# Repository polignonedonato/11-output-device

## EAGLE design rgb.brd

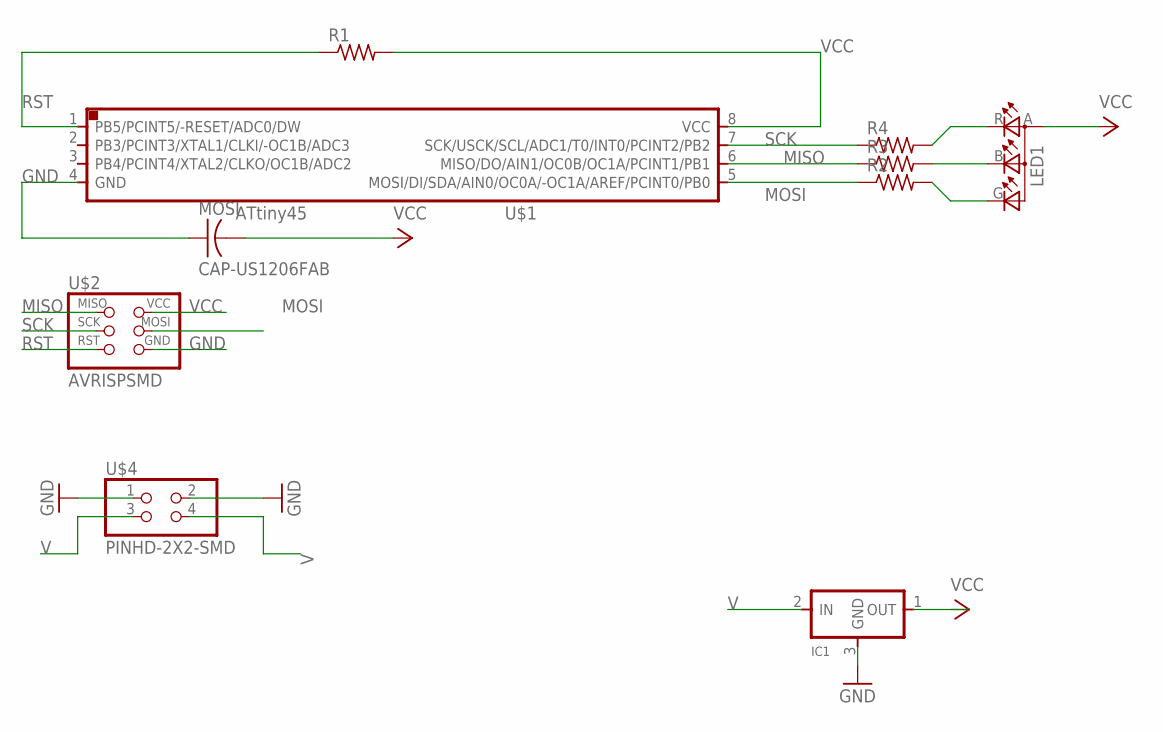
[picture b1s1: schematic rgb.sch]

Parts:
IC1: REGULATORSOT23; SOT23
LED1: LEDRGBOLD; P-LCC-4-3
MOSI: CAP-US1206FAB; C1206FAB
R1, R2, R3, R4: RES-US1206FAB; R1206FAB
U$1: ATTINY45SI; SOIC8
U$2: AVRISPSMD; 2X03SMD
U$4: PINHD-2X2-SMD; 2X02SMD

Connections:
GND: IC1.3 (GND), MOSI.1, U$1.4 (GND), U$2.6 (GND), U$4.1, U$4.2
MISO: R3.1, U$1.6 (MISO/DO/AIN1/OC0B/OC1A/PCINT1/PB1), U$2.1 (MISO)
MOSI: R2.1, U$1.5 (MOSI/DI/SDA/AIN0/OC0A/-OC1A/AREF/PCINT0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), U$2.4 (MOSI)
unnamed: LED1.R (CRED), R4.2
unnamed: LED1.G (CGREEN), R2.2
unnamed: LED1.B (CBLUE), R3.2
RST: R1.1, U$1.1 (PB5/PCINT5/-RESET/ADC0/DW), U$2.5 (RST)
SCK: R4.1, U$1.7 (SCK/USCK/SCL/ADC1/T0/INT0/PCINT2/PB2), U$2.3 (SCK)
V: IC1.2 (IN), U$4.3, U$4.4
VCC: LED1.A (A2), MOSI.2, R1.2, U$1.8 (VCC), U$2.2 (VCC)

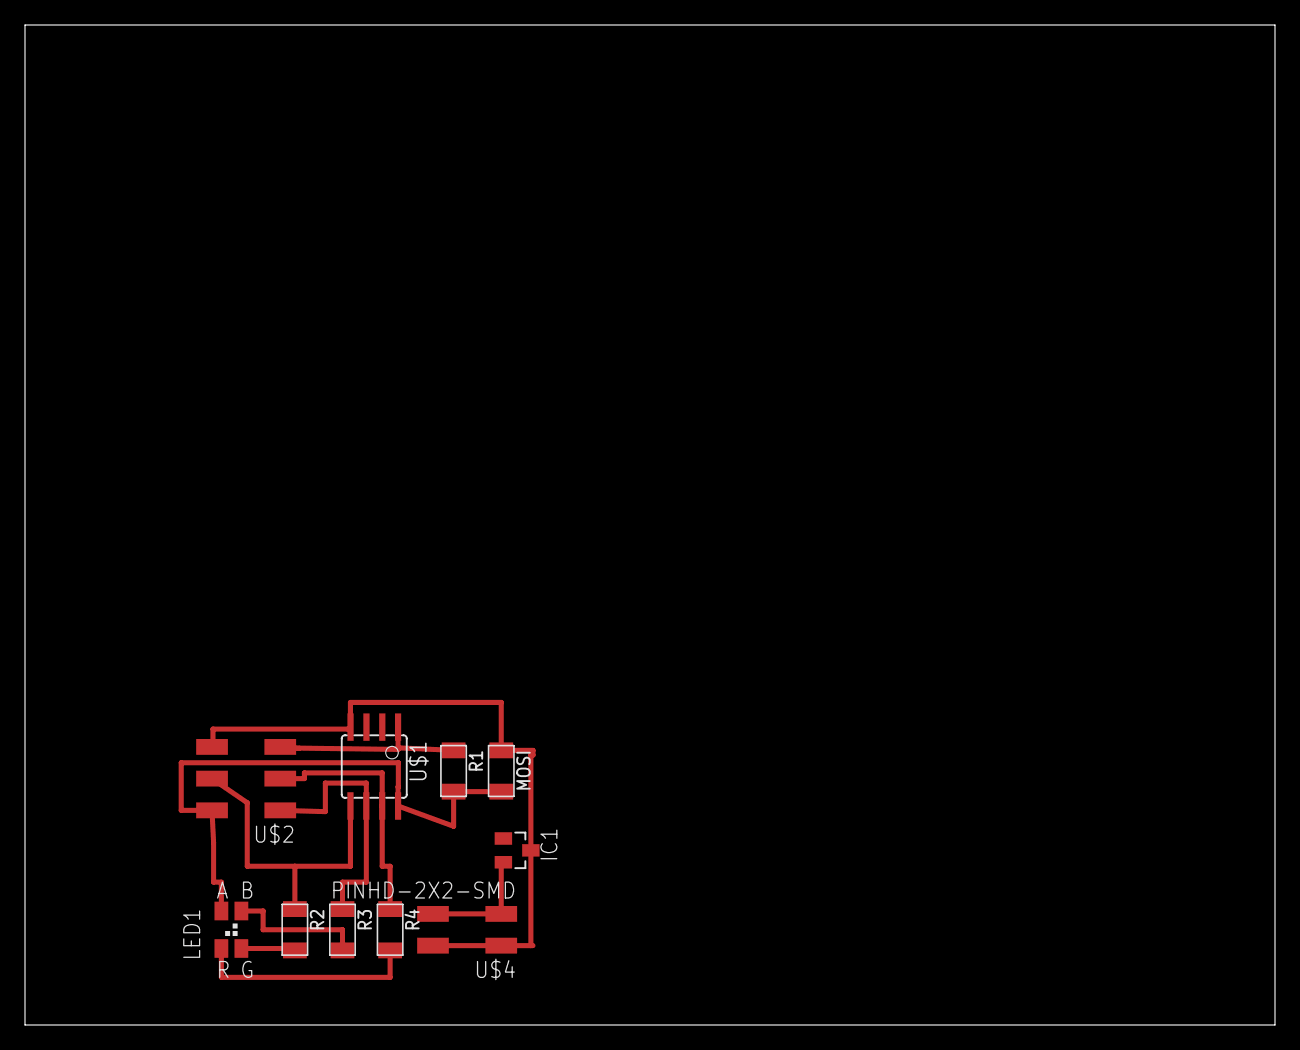
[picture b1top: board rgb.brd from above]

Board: 2 copper layers, 100.0 x 80.0 mm, 10 parts (0 on the bottom side), 10 nets.

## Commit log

2016-07-12 output device
    outputdevice
